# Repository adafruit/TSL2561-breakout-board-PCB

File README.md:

## TSL2561 breakout board PCB

<a href="http://www.adafruit.com/products/1980"><br/>
Click picture or link below to purchase one from the Adafruit shop</a>

PCB CAD files for the Adafruit TSL2591 High Dynamic Range Digital Light Sensor. 
PCB format is EagleCAD schematic and board layout

For more details, check out the product page at
* https://www.adafruit.com/products/1980

### Description

When the future is dazzlingly-bright, this ultra-high-range luminosity sensor will help you measure it. The TSL2591 luminosity sensor is an advanced digital light sensor, ideal for use in a wide range of light situations. Compared to low cost CdS cells, this sensor is more precise, allowing for exact lux calculations and can be configured for different gain/timing ranges to detect light ranges from 188 uLux up to 88,000 Lux on the fly.

The best part of this sensor is that it contains both infrared and full spectrum diodes! That means you can separately measure infrared, full-spectrum or human-visible light. Most sensors can only detect one or the other, which does not accurately represent what human eyes see (since we cannot perceive the IR light that is detected by most photo diodes) This sensor is much like the TSL2561 but with a wider range (and the interface code is different). This sensor has a massive 600,000,000:1 dynamic range! Unlike the TSL2561 you cannot change the I2C address, so keep that in mind.

The built in ADC means you can use this with any microcontroller, even if it doesn't have analog inputs. The current draw is extremely low, so its great for low power data-logging systems. about 0.4mA when actively sensing, and less than 5 uA when in power-down mode.

### License

Adafruit invests time and resources providing this open source design, please support Adafruit and open-source hardware by purchasing products from [Adafruit](https://www.adafruit.com)!

Designed by Limor Fried/Ladyada for Adafruit Industries.

Creative Commons Attribution/Share-Alike, all text above must be included in any redistribution. See license.txt for additional details.

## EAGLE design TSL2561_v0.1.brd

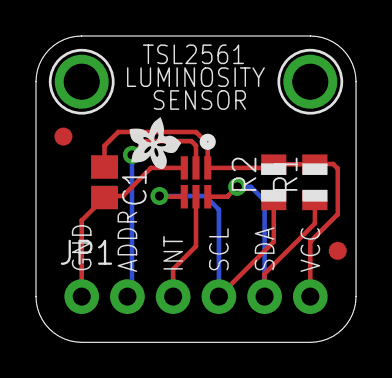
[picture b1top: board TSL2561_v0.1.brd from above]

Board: 2 copper layers, 17.8 x 17.0 mm, 10 parts (0 on the bottom side), 6 nets.

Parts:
C1: 0.1uF; C0805
JP1: 1X06_ROUND_76
R1, R2: 10K; R0805
U1: TSL2561; TSL2561_FN
U$2, U$4: FIDUCIAL; FIDUCIAL_1MM
U$5, U$6: MOUNTINGHOLE2.0; MOUNTINGHOLE_2.0_PLATED
U$7: ADAFRUIT200MIL

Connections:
ADDR: JP1.2, U1.ADR
GND: C1.2, JP1.1, U1.VSS
INT: JP1.3, U1.INT
SCL: JP1.4, R2.1, U1.CLK
SDA: JP1.5, R1.1, U1.DATA
VCC: C1.1, JP1.6, R1.2, R2.2, U1.VDD

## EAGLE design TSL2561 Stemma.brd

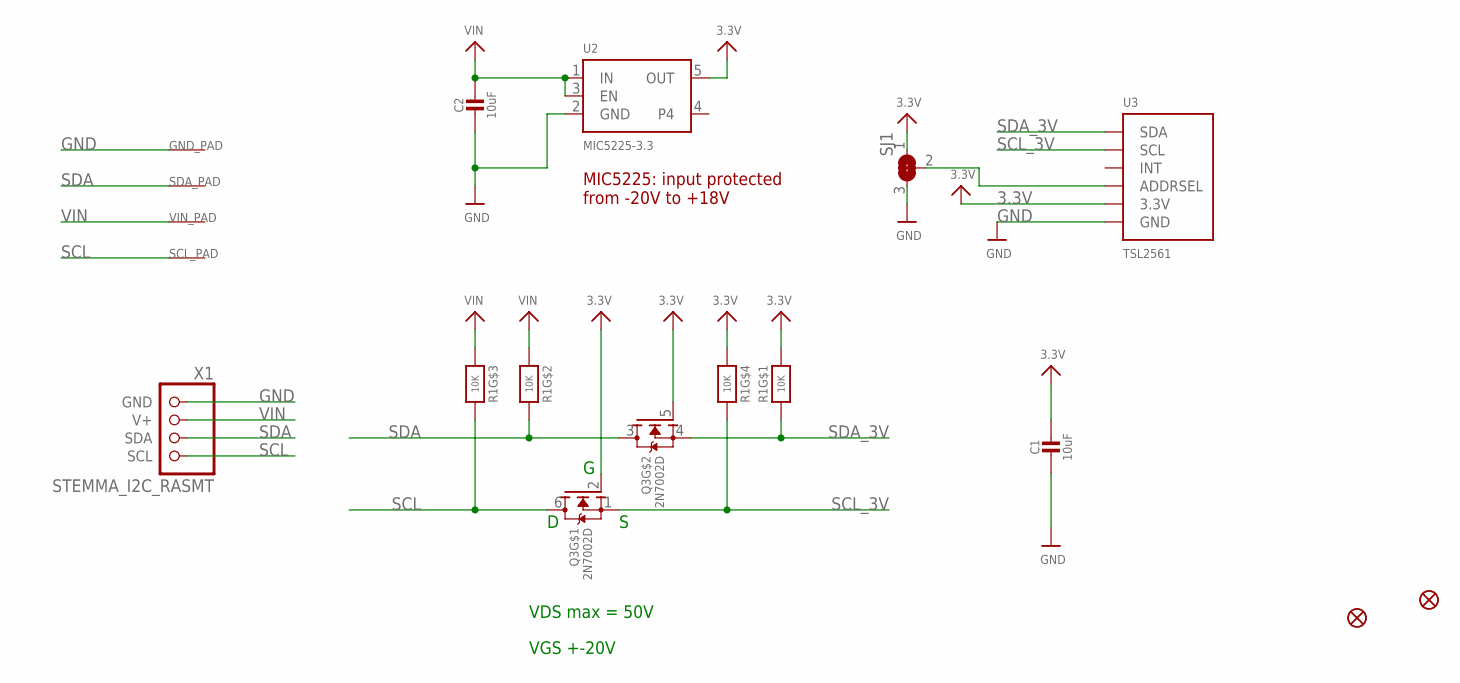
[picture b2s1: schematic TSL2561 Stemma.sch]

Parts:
C1, C2: 10uF; 0805-NO
FID1, FID2: FIDUCIAL_1MM
GND_PAD: SEWTAP-ALLIGATOR; SEWALLI
Q3: 2N7002D; SOT363
R1: 10K; RESPACK_4X0603
SCL_PAD: SEWTAP-ALLIGATOR; SEWALLI
SDA_PAD: SEWTAP-ALLIGATOR; SEWALLI
SJ1: SOLDERJUMPER_2WAY; SOLDERJUMPER_2WAY_OPEN_NOPASTE
U2: MIC5225-3.3; SOT23-5
U3: TSL2561; TSL2561_FN
VIN_PAD: SEWTAP-ALLIGATOR; SEWALLI
X1: STEMMA_I2C_RASMT; JSTPH4

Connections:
3.3V: C1.1, Q3.2 (G), Q3.5 (G), R1.1, R1.5 (2), SJ1.1, U2.5 (OUT), U3.VDD (3.3V)
GND: C1.2, C2.2, GND_PAD.P$1, SJ1.3, U2.2 (GND), U3.VSS (GND), X1.1 (GND)
unnamed: SJ1.2, U3.ADR (ADDRSEL)
SCL: Q3.6 (D), R1.6 (2), SCL_PAD.P$1, X1.4 (SCL)
SCL_3V: Q3.1 (S), R1.4 (1), U3.CLK (SCL)
SDA: Q3.3 (D), R1.7 (2), SDA_PAD.P$1, X1.3 (SDA)
SDA_3V: Q3.4 (S), R1.8 (2), U3.DATA (SDA)
VIN: C2.1, R1.2 (1), R1.3 (1), U2.1 (IN), U2.3 (EN), VIN_PAD.P$1, X1.2 (V+)

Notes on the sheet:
MIC5225: input protected from -20V to +18V
VDS max = 50V
VGS +-20V

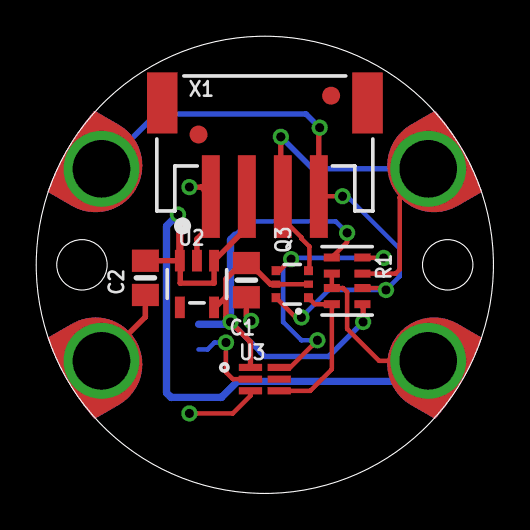
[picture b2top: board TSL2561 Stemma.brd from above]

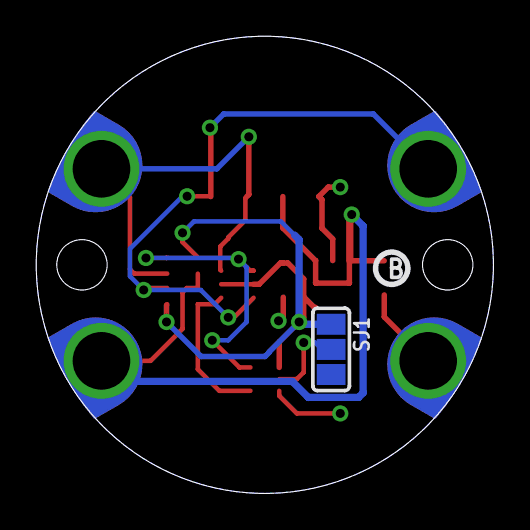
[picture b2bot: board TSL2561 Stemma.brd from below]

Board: 2 copper layers, 25.4 x 25.4 mm, 17 parts (3 on the bottom side), 8 nets.

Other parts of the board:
U$4: STEMMA_TSL2561_B_FRONT
U$7: STEMMA_TSL2561_B_BACK
U$8: PCBFEAT-REV-040

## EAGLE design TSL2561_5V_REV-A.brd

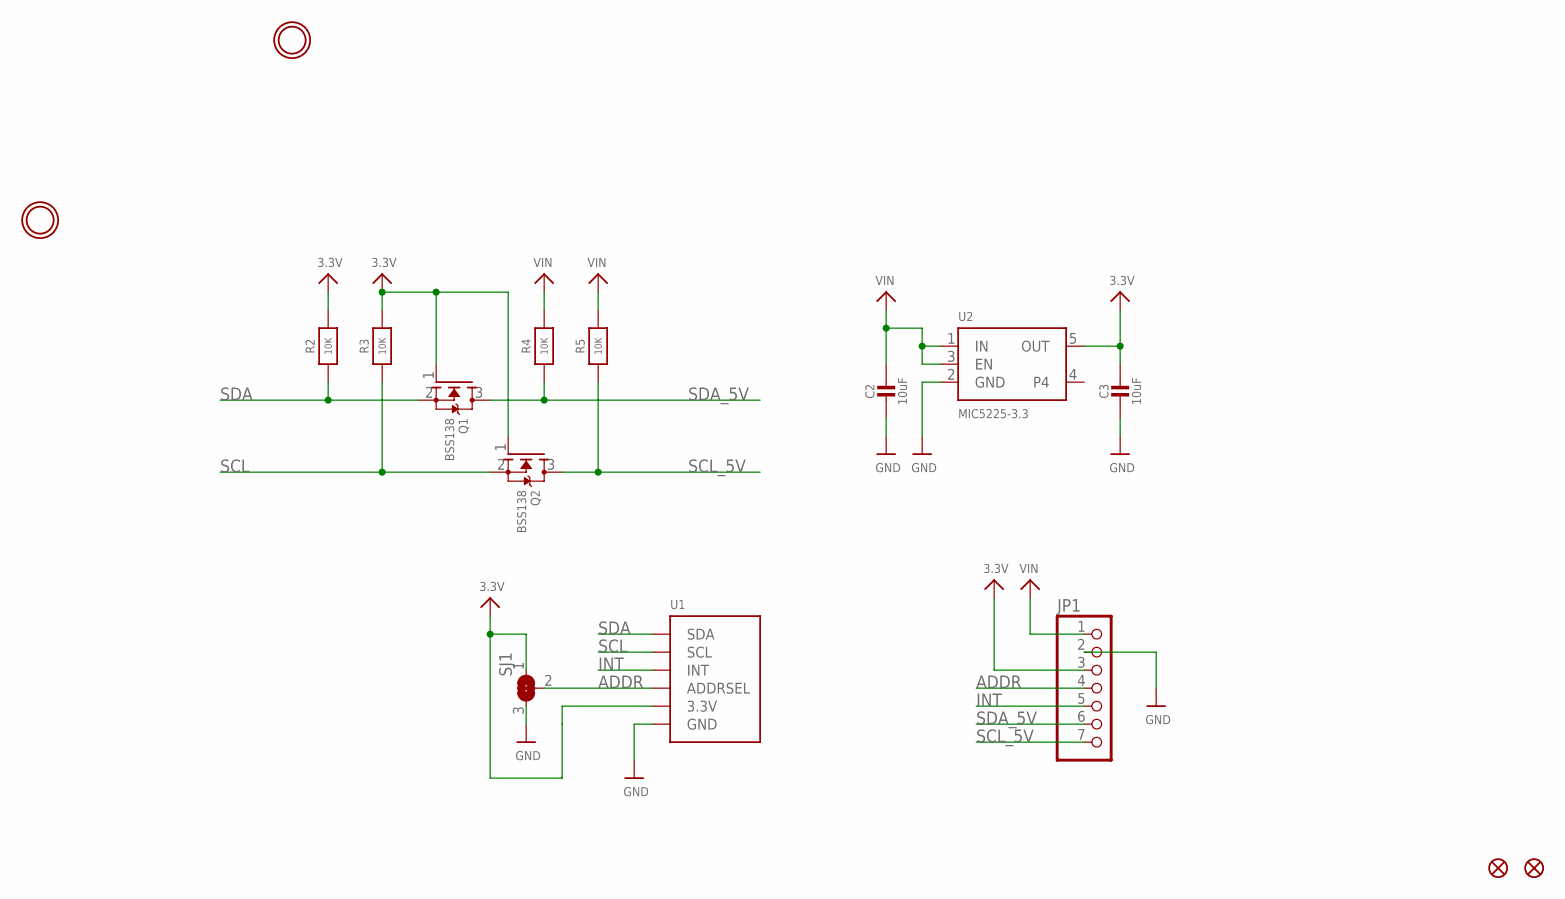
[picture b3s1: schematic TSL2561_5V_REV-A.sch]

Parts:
C2, C3: 10uF; 0805-NO
FID1, FID2: FIDUCIAL""; FIDUCIAL_1MM
JP1: HEADER-1X7THICKER; 1X07_ROUND_76
Q1, Q2: BSS138; SOT23-WIDE
R2, R3, R4, R5: 10K; 0805-NO
SJ1: SOLDERJUMPER_2WAY; SOLDERJUMPER_2WAY_OPEN_NOPASTE
U1: LIGHT_TSL2561; TSL2561_FN
U2: MIC5225-3.3; SOT23-5
U$18, U$19: MOUNTINGHOLE2.5; MOUNTINGHOLE_2.5_PLATED

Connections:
3.3V: C3.1, JP1.3, Q1.1 (G), Q2.1 (G), R2.2, R3.2, SJ1.1, U1.VDD (3.3V), U2.5 (OUT)
ADDR: JP1.4, SJ1.2, U1.ADR (ADDRSEL)
GND: C2.2, C3.2, JP1.2, SJ1.3, U1.VSS (GND), U2.2 (GND)
INT: JP1.5, U1.INT
SCL: Q2.2 (S), R3.1, U1.CLK (SCL)
SCL_5V: JP1.7, Q2.3 (D), R5.1
SDA: Q1.2 (S), R2.1, U1.DATA (SDA)
SDA_5V: JP1.6, Q1.3 (D), R4.1
VIN: C2.1, JP1.1, R4.2, R5.2, U2.1 (IN), U2.3 (EN)

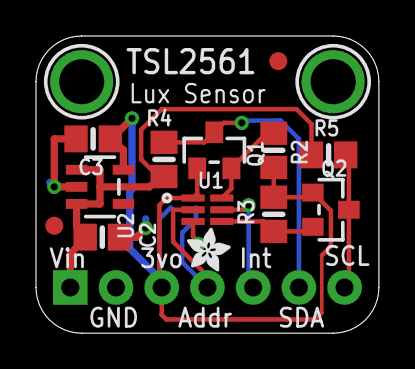
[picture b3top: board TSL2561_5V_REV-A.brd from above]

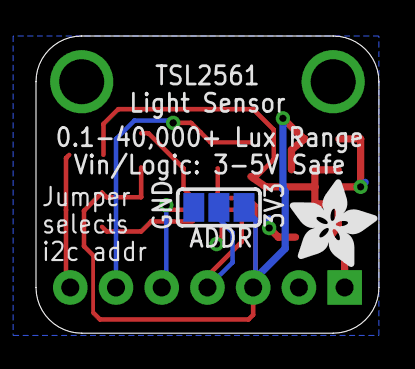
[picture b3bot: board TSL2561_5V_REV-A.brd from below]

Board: 2 copper layers, 19.1 x 16.5 mm, 18 parts (2 on the bottom side), 9 nets.

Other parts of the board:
U$15: ADAFRUIT_2.5MM
U$20: ADAFRUIT_5MM

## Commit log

2011-08-29 release layout files
2014-06-17 5V version
2018-01-02 stemma pcbs
2026-06-03 update file format to XML

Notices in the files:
parts and their libraries:
microbuilder: This work is placed in the public domain, and may be freely used for commercial and non-commercial work with the following conditions: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
